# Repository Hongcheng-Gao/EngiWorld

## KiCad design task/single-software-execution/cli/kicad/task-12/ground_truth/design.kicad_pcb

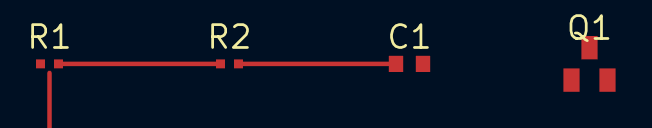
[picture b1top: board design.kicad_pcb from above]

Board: 2 copper layers, 4 parts (0 on the bottom side), 3 nets.

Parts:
C1: 100nF; C_0603
Q1: 2N7002; SOT-23
R1: 10k; R_0402
R2: 22k; R_0402

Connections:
GND: C1.2, Q1.1, R1.2
SIG_A: Q1.2, R2.2
VCC: C1.1, Q1.3, R1.1, R2.1

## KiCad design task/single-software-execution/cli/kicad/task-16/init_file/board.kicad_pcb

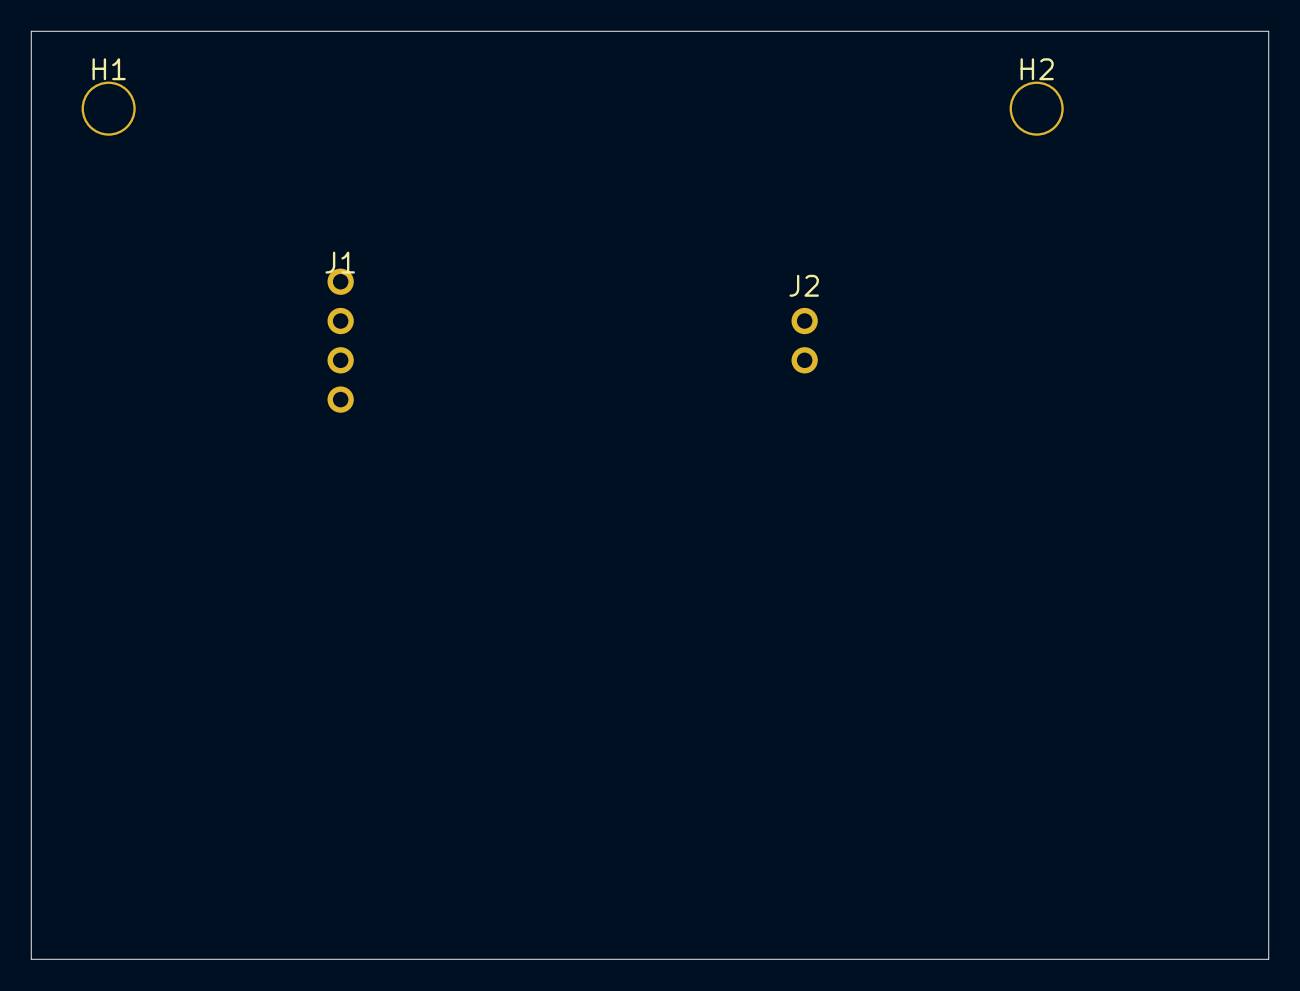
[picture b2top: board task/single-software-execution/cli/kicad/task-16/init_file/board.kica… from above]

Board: 2 copper layers, 80.0 x 60.0 mm, 4 parts (0 on the bottom side), 2 nets, no tracks yet.

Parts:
H1, H2: MH; MountingHole_3.2mm_M3
J1: HDR_4; PinHeader_1x04_P2.54mm_Vertical
J2: HDR_2; PinHeader_1x02_P2.54mm_Vertical

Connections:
GND: J1.1, J1.3, J2.1
VCC: J1.2, J1.4, J2.2

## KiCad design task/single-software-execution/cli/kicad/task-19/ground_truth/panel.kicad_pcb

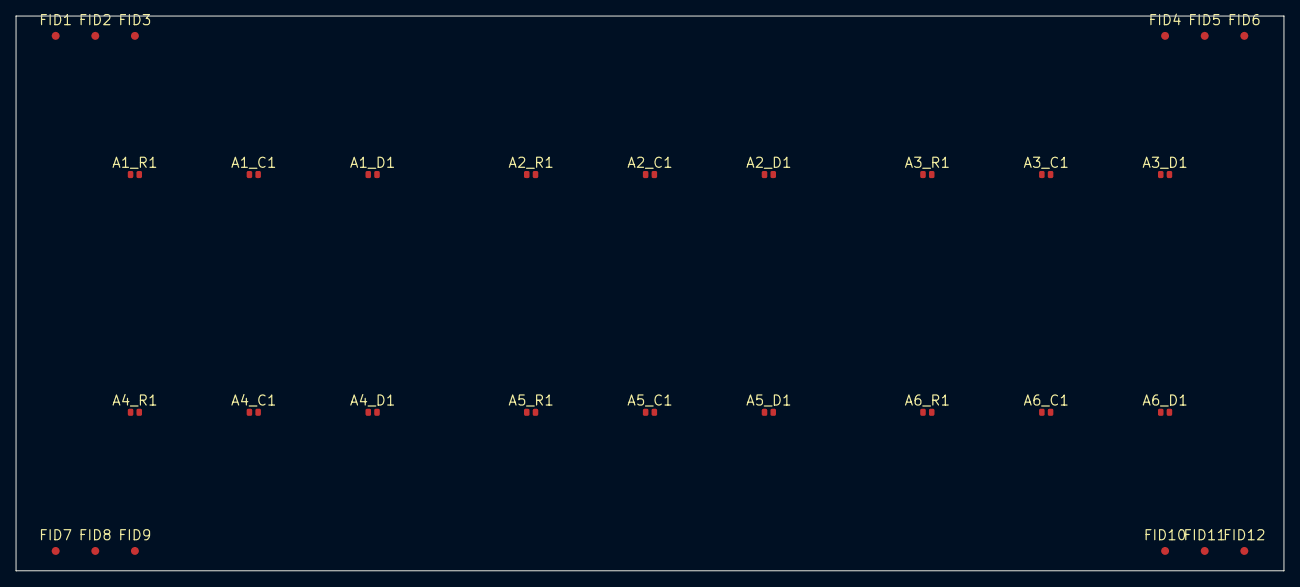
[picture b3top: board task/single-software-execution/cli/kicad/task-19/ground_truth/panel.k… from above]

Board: 2 copper layers, 160.0 x 70.0 mm, 30 parts (0 on the bottom side), 3 nets, no tracks yet.

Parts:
A1_C1, A2_C1, A3_C1, A4_C1, A5_C1, A6_C1: 100nF; C_0402
A1_D1, A2_D1, A3_D1, A4_D1, A5_D1, A6_D1: LED_G; LED_0402
A1_R1, A2_R1, A3_R1, A4_R1, A5_R1, A6_R1: 10k; R_0402
FID1, FID2, FID3, FID4, FID5, FID6, FID7, FID8, FID9, FID10, FID11, FID12: Fiducial; Fiducial_1mm_Mask2mm

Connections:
GND: A1_C1.2, A1_D1.2, A2_C1.2, A2_D1.2, A3_C1.2, A3_D1.2, A4_C1.2, A4_D1.2, A5_C1.2, A5_D1.2, A6_C1.2, A6_D1.2
SIG: A1_D1.1, A1_R1.2, A2_D1.1, A2_R1.2, A3_D1.1, A3_R1.2, A4_D1.1, A4_R1.2, A5_D1.1, A5_R1.2, A6_D1.1, A6_R1.2
VCC: A1_C1.1, A1_R1.1, A2_C1.1, A2_R1.1, A3_C1.1, A3_R1.1, A4_C1.1, A4_R1.1, A5_C1.1, A5_R1.1, A6_C1.1, A6_R1.1

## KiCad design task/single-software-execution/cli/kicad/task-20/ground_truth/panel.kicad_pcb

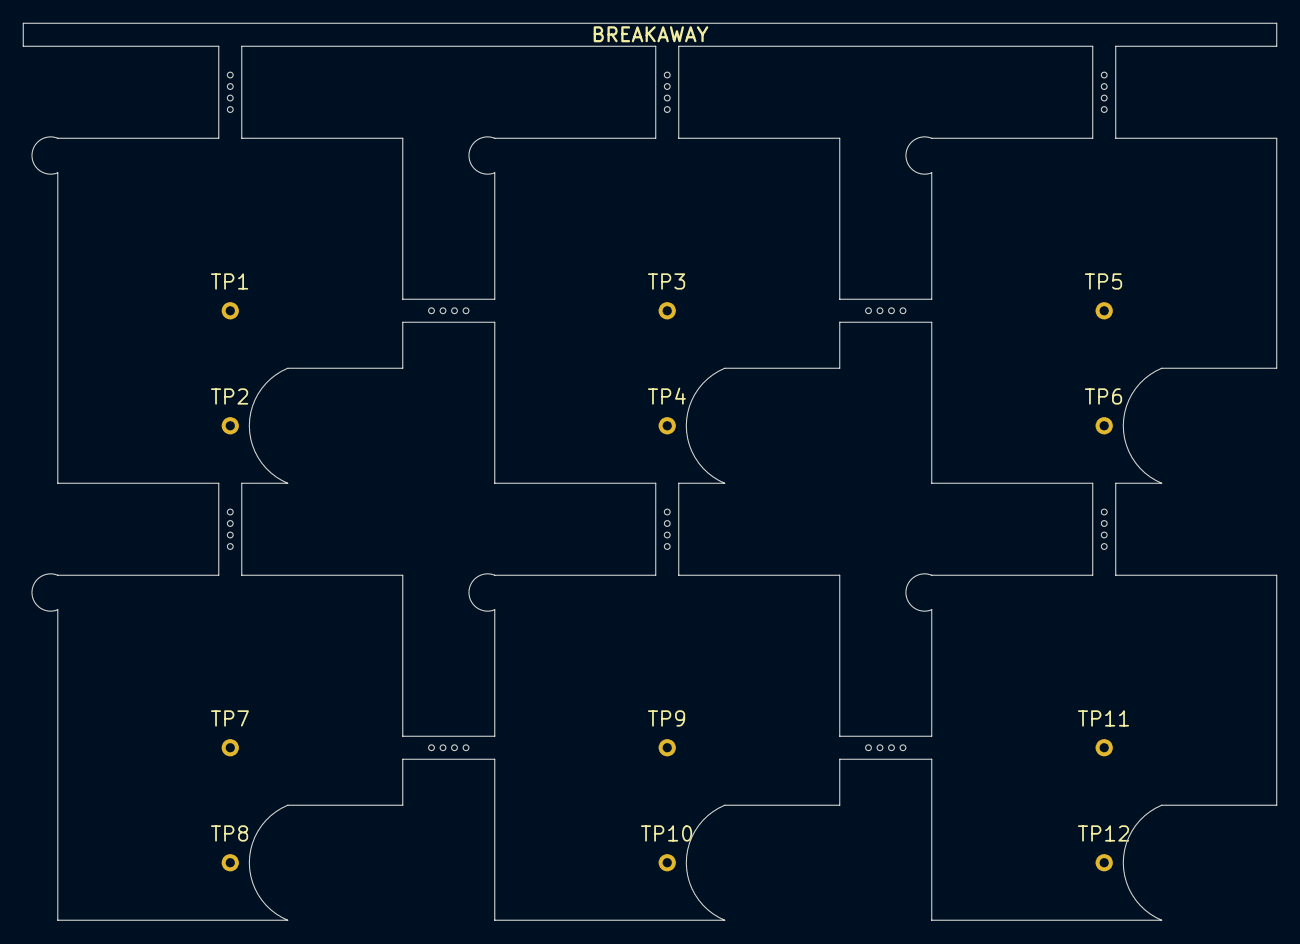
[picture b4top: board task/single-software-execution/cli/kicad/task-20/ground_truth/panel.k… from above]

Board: 2 copper layers, 109.0 x 78.0 mm, 22 parts (0 on the bottom side), 2 nets, no tracks yet.

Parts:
MB1, MB2, MB3, MB4, MB5, MB6, MB7, MB8, MB9, MB10: MouseBiteArray
TP1, TP2, TP3, TP4, TP5, TP6, TP7, TP8, TP9, TP10, TP11, TP12: TP; TestPoint_Pad_D1.5mm

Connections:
GND: TP2.1, TP4.1, TP6.1, TP8.1, TP10.1, TP12.1
VCC: TP1.1, TP3.1, TP5.1, TP7.1, TP9.1, TP11.1

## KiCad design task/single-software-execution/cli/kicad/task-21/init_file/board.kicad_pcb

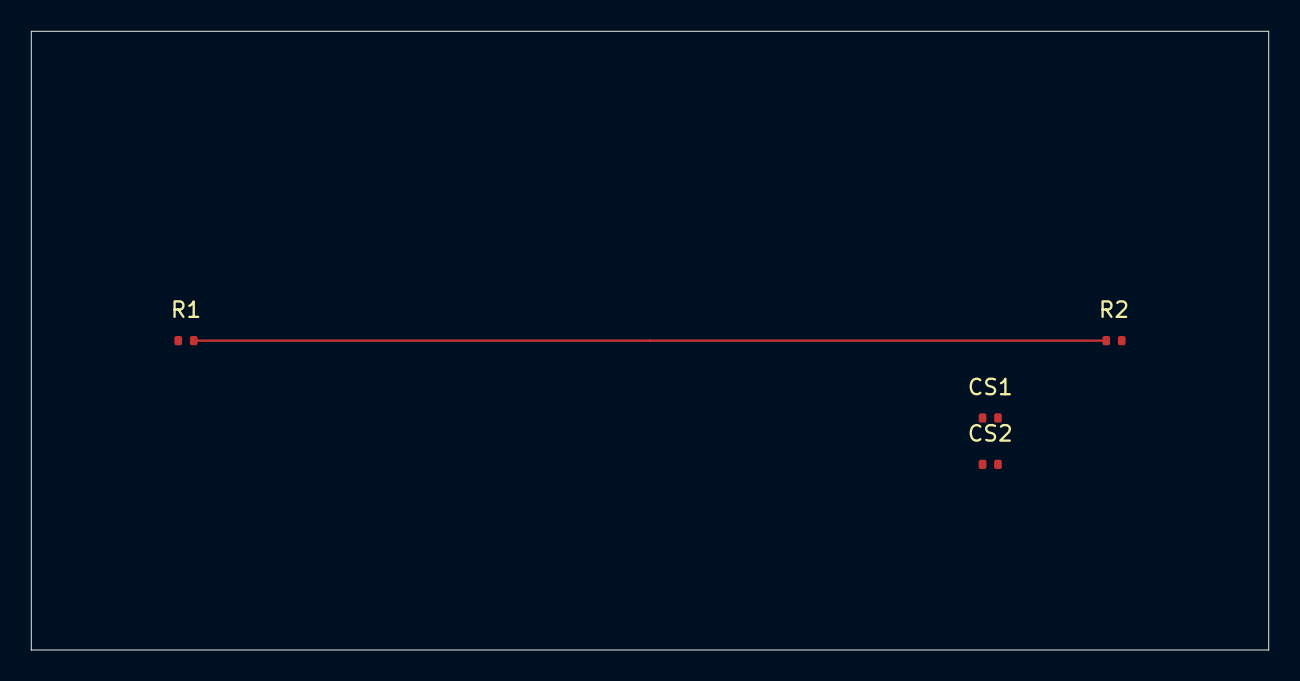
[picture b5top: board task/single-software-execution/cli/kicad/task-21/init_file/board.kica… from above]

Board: 4 copper layers, 80.0 x 40.0 mm, 4 parts (0 on the bottom side), 3 nets.

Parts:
CS1, CS2: 100n; C_0402
R1, R2: 100; R_0402

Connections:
+3V3: CS1.2, CS2.2
GND: CS1.1, CS2.1
HS1: R1.1, R1.2, R2.1, R2.2
